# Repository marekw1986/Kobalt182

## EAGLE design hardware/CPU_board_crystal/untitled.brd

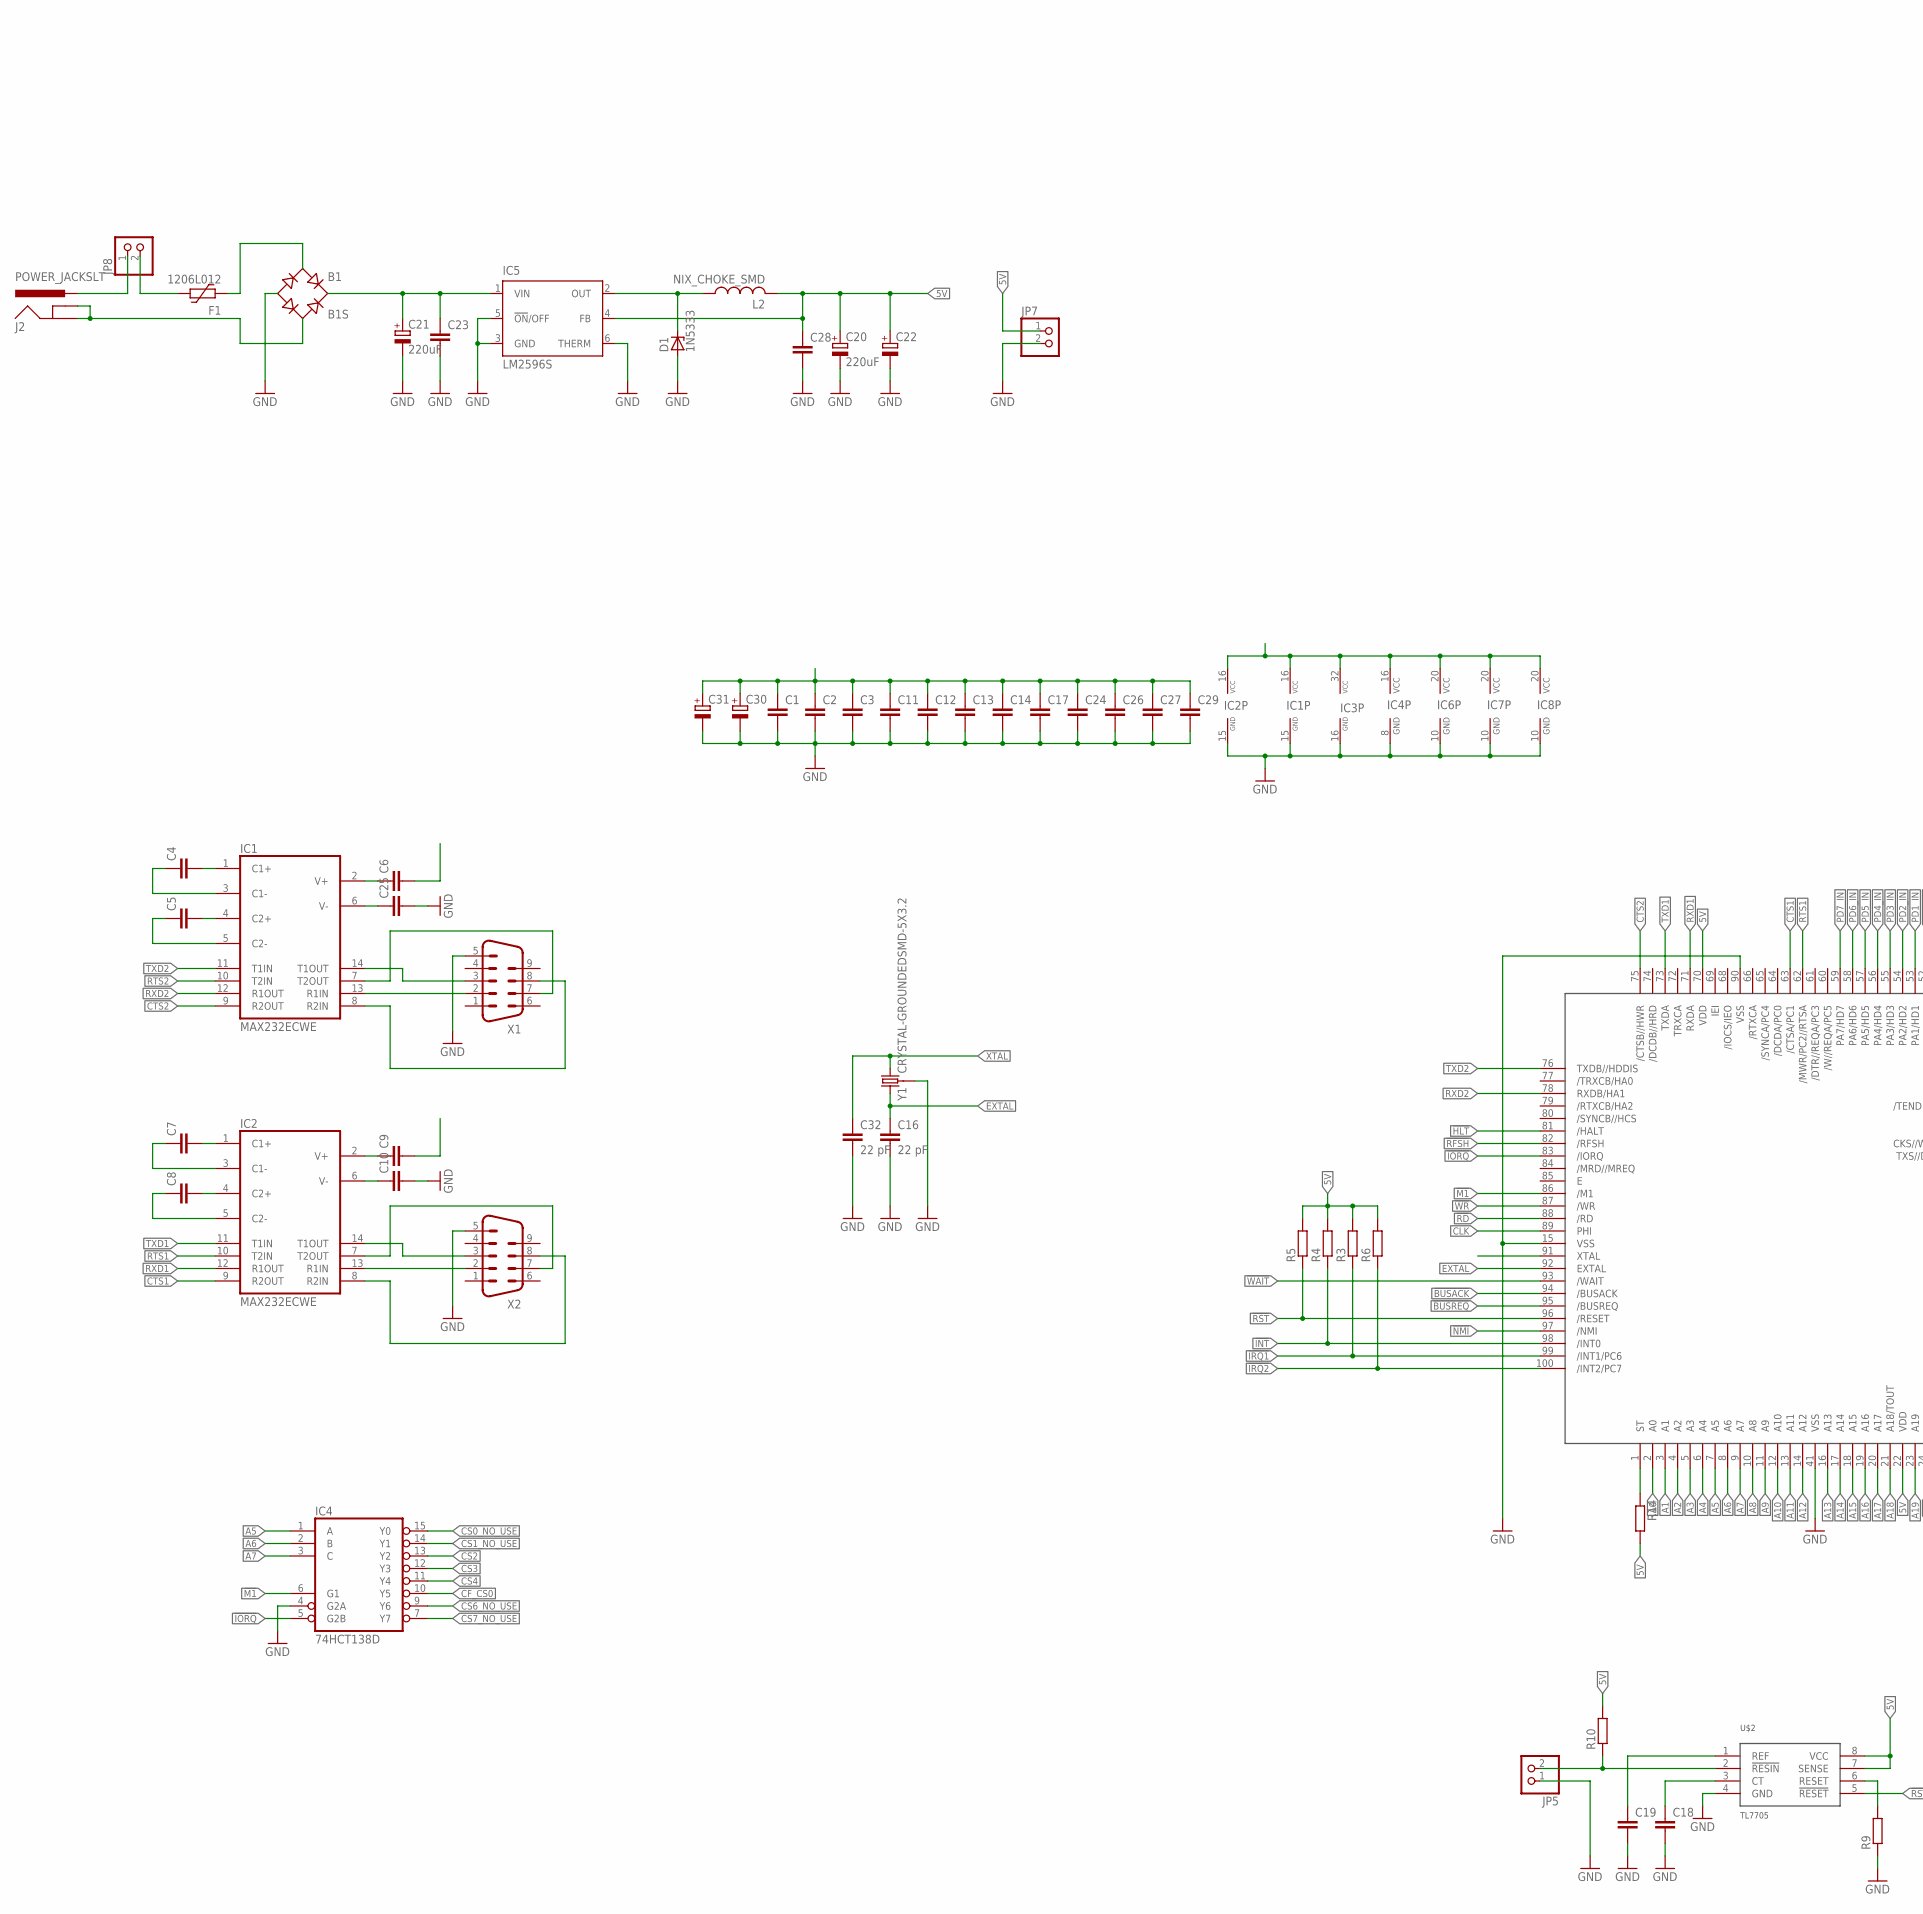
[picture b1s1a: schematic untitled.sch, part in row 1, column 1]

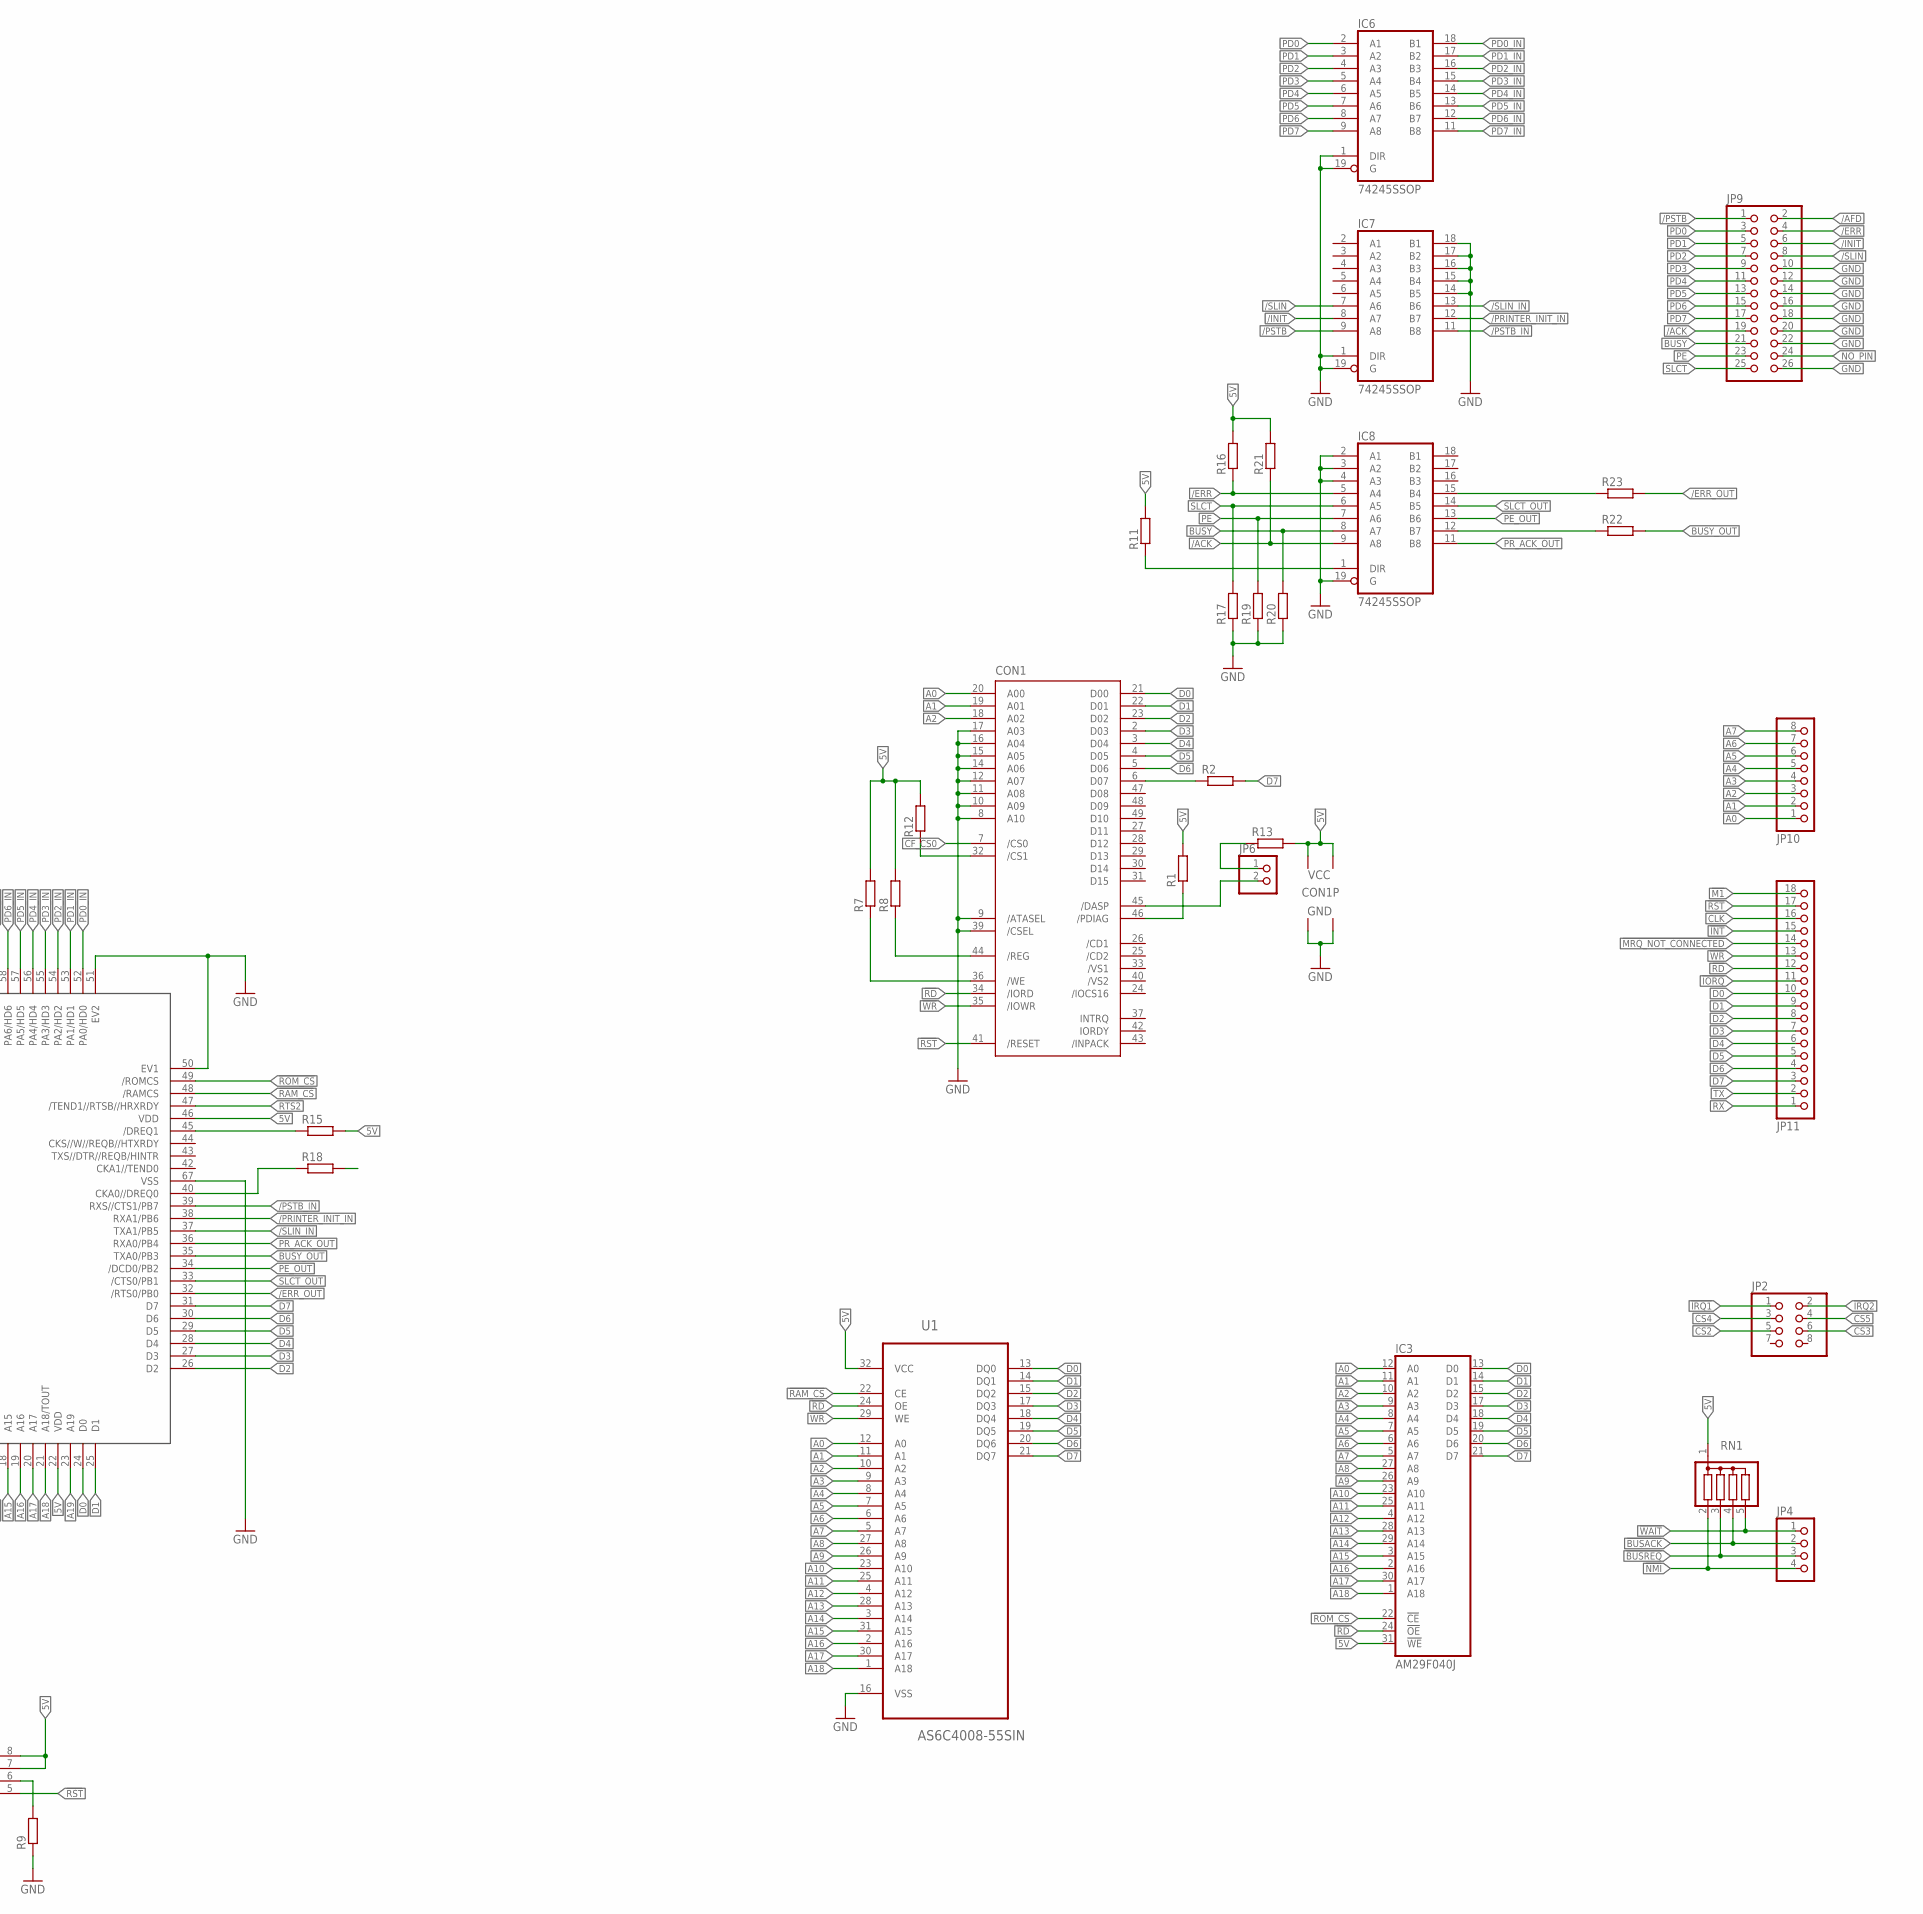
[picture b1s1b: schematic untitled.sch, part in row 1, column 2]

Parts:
B1: B1S; MBS
C1, C2, C4, C5, C6, C7, C8, C9, C10, C11, C12, C14, C17, C18, C19, C23, C24, C25, C28, C29: C-EUC0603; C0603
C3, C13, C26, C27: C-EUC0402; C0402
C16, C32: 22 pF; C0603
C20, C21: 220uF; 153CLV-0810
C22: CPOL-EUSMCC; SMC_C
C30, C31: CPOL-EUSMCB; SMC_B
CON1: CF-CARD-IDE_MODE; MI20-50PD-SF
D1: 1N5333; C1702-15
F1: 1206L012; 1206L
IC1, IC2: MAX232ECWE; SO16L
IC3: AM29F040J; PLCC32R
IC4: 74HCT138D; SO16
IC5: LM2596S; TO263-5
IC6, IC7, IC8: 74245SSOP; SSOP20
J2: POWER_JACKSLT; POWER_JACK_SLOT
JP2: PINHD-2X4; 2X04
JP4: PINHD-1X4; 1X04
JP5, JP6, JP7, JP8: PINHD-1X2; 1X02
JP9: PINHD-2X13_2.54-SMD; 2X13SMD
JP10: PINHD-1X8; 1X08
JP11: PINHD-1X18; 1X18
L2: NIX_CHOKE_SMD
R1, R2, R4, R6, R7, R8, R9, R11, R12, R13, R16, R17, R19, R20, R21: R-EU_R0603; R0603
R3, R15, R18, R22, R23: R-EU_R0402; R0402
R5: R-EU_R1206; R1206
R10: R-EU_M1206; M1206
R14: R-EU_0204/5; 0204/5
RN1: G04R; SIL5
U1: AS6C4008-55SIN; SOIC127P1407X299-32N
U$1: Z80182; TQFP100
U$2: TL7705; SOIC8
X1, X2: M09HP
Y1: CRYSTAL-GROUNDEDSMD-5X3.2; CRYSTAL-SMD-5X3.2-4PAD

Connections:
5V: C1.1, C2.1, C3.1, C6.2, C9.2, C11.1, C12.1, C13.1, C14.1, C17.1, C20.+, C22.+, C24.1, C26.1, C27.1, C28.1, C29.1, C30.+, C31.+, CON1.13 (VCC2), CON1.38 (VCC1), IC1.16 (VCC), IC2.16 (VCC), IC3.31 (!WE), IC3.32 (VCC), IC4.16 (VCC), IC5.4 (FB), IC6.20 (VCC), IC7.20 (VCC), IC8.20 (VCC), JP7.1, L2.P$2 (2), R1.2, R3.2, R4.2, R5.2, R6.2, R7.2, R8.2, R10.2, R11.2, R12.2, R13.2, R14.2, R15.2, R16.2, R18.2, R21.2, RN1.1, U1.32 (VCC), U$1.22 (VDD), U$1.46 (VDD), U$1.70 (VDD), U$2.7 (SENSE), U$2.8 (VCC)
!BUSACK: JP4.2, RN1.4, U$1.94 (/BUSACK)
!BUSREQ: JP4.3, RN1.3, U$1.95 (/BUSREQ)
!HLT: U$1.81 (/HALT)
!INT: JP11.15, R4.1, U$1.98 (/INT0)
!IORQ: IC4.5 (G2B), JP11.11, U$1.83 (/IORQ)
!IRQ1: JP2.1, R3.1, U$1.99 (/INT1/PC6)
!IRQ2: JP2.2, R6.1, U$1.100 (/INT2/PC7)
!M1: IC4.6 (G1), JP11.18, U$1.86 (/M1)
!MRQ_NOT_CONNECTED: JP11.14
!NMI: JP4.4, RN1.2, U$1.97 (/NMI)
!RAM_CS: U1.22 (CE), U$1.48 (/RAMCS)
!RD: CON1.34 (/IORD), IC3.24 (!OE), JP11.12, U1.24 (OE), U$1.88 (/RD)
!RFSH: U$1.82 (/RFSH)
!ROM_CS: IC3.22 (!CE), U$1.49 (/ROMCS)
!RST: CON1.41 (/RESET), JP11.17, R5.1, U$1.96 (/RESET), U$2.5 (!RESET)
!WAIT: JP4.1, RN1.5, U$1.93 (/WAIT)
!WR: CON1.35 (/IOWR), JP11.13, U1.29 (WE), U$1.87 (/WR)
/ACK: IC8.9 (A8), JP9.19, R21.1
/AFD: JP9.2
/ERR: IC8.5 (A4), JP9.4, R16.1
/ERR_OUT: R23.2, U$1.32 (/RTS0/PB0)
/INIT: IC7.8 (A7), JP9.6
/PRINTER_INIT_IN: IC7.12 (B7), U$1.38 (RXA1/PB6)
/PSTB: IC7.9 (A8), JP9.1
/PSTB_IN: IC7.11 (B8), U$1.39 (RXS//CTS1/PB7)
/SLIN: IC7.7 (A6), JP9.8
/SLIN_IN: IC7.13 (B6), U$1.37 (TXA1/PB5)
A0: CON1.20 (A00), IC3.12 (A0), JP10.1, U1.12 (A0), U$1.2 (A0)
A1: CON1.19 (A01), IC3.11 (A1), JP10.2, U1.11 (A1), U$1.3 (A1)
A2: CON1.18 (A02), IC3.10 (A2), JP10.3, U1.10 (A2), U$1.4 (A2)
A3: IC3.9 (A3), JP10.4, U1.9 (A3), U$1.5 (A3)
A4: IC3.8 (A4), JP10.5, U1.8 (A4), U$1.6 (A4)
A5: IC3.7 (A5), IC4.1 (A), JP10.6, U1.7 (A5), U$1.7 (A5)
A6: IC3.6 (A6), IC4.2 (B), JP10.7, U1.6 (A6), U$1.8 (A6)
A7: IC3.5 (A7), IC4.3 (C), JP10.8, U1.5 (A7), U$1.9 (A7)
A8: IC3.27 (A8), U1.27 (A8), U$1.10 (A8)
A9: IC3.26 (A9), U1.26 (A9), U$1.11 (A9)
A10: IC3.23 (A10), U1.23 (A10), U$1.12 (A10)
A11: IC3.25 (A11), U1.25 (A11), U$1.13 (A11)
A12: IC3.4 (A12), U1.4 (A12), U$1.14 (A12)
A13: IC3.28 (A13), U1.28 (A13), U$1.16 (A13)
A14: IC3.29 (A14), U1.3 (A14), U$1.17 (A14)
A15: IC3.3 (A15), U1.31 (A15), U$1.18 (A15)
A16: IC3.2 (A16), U1.2 (A16), U$1.19 (A16)
A17: IC3.30 (A17), U1.30 (A17), U$1.20 (A17)
A18: IC3.1 (A18), U1.1 (A18), U$1.21 (A18/TOUT)
A19: U$1.23 (A19)
BUSY: IC8.8 (A7), JP9.21, R20.2
BUSY_OUT: R22.2, U$1.35 (TXA0/PB3)
CF_CS0: CON1.7 (/CS0), IC4.10 (Y5)
CLK: JP11.16, U$1.89 (PHI)
CS0_NO_USE: IC4.15 (Y0)
CS1_NO_USE: IC4.14 (Y1)
CS2: IC4.13 (Y2), JP2.5
CS3: IC4.12 (Y3), JP2.6
CS4: IC4.11 (Y4), JP2.3
CS5: JP2.4
CS6_NO_USE: IC4.9 (Y6)
CS7_NO_USE: IC4.7 (Y7)
CTS1: IC2.9 (R2OUT), U$1.63 (/CTSA/PC1)
CTS2: IC1.9 (R2OUT), U$1.75 (/CTSB//HWR)
D0: CON1.21 (D00), IC3.13 (D0), JP11.10, U1.13 (DQ0), U$1.24 (D0)
D1: CON1.22 (D01), IC3.14 (D1), JP11.9, U1.14 (DQ1), U$1.25 (D1)
D2: CON1.23 (D02), IC3.15 (D2), JP11.8, U1.15 (DQ2), U$1.26 (D2)
D3: CON1.2 (D03), IC3.17 (D3), JP11.7, U1.17 (DQ3), U$1.27 (D3)
D4: CON1.3 (D04), IC3.18 (D4), JP11.6, U1.18 (DQ4), U$1.28 (D4)
D5: CON1.4 (D05), IC3.19 (D5), JP11.5, U1.19 (DQ5), U$1.29 (D5)
D6: CON1.5 (D06), IC3.20 (D6), JP11.4, U1.20 (DQ6), U$1.30 (D6)
D7: IC3.21 (D7), JP11.3, R2.2, U1.21 (DQ7), U$1.31 (D7)
EXTAL: C16.1, U$1.92 (EXTAL), Y1.3 (1)
GND: B1.-, C1.2, C2.2, C3.2, C10.2, C11.2, C12.2, C13.2, C14.2, C16.2, C17.2, C18.2, C19.2, C20.-, C21.-, C22.-, C23.2, C24.2, C25.2, C26.2, C27.2, C28.2, C29.2, C30.-, C31.-, C32.2, CON1.1 (GND1), CON1.8 (A10), CON1.9 (/ATASEL), CON1.10 (A09), CON1.11 (A08), CON1.12 (A07), CON1.14 (A06), CON1.15 (A05), CON1.16 (A04), CON1.17 (A03), CON1.39 (/CSEL), CON1.50 (GND2), D1.A, IC1.15 (GND), IC2.15 (GND), IC3.16 (GND), IC4.4 (G2A), IC4.8 (GND), IC5.3 (GND), IC5.5 (!ON!/OFF), IC5.6 (THERM), IC6.1 (DIR), IC6.10 (GND), IC6.19 (G), IC7.1 (DIR), IC7.10 (GND), IC7.14 (B5), IC7.15 (B4), IC7.16 (B3), IC7.17 (B2), IC7.18 (B1), IC7.19 (G), IC8.2 (A1), IC8.3 (A2), IC8.4 (A3), IC8.10 (GND), IC8.19 (G), JP5.1, JP7.2, JP9.10, JP9.12, JP9.14, JP9.16, JP9.18, JP9.20, JP9.22, JP9.26, R9.1, R17.1, R19.1, R20.1, U1.16 (VSS), U$1.15 (VSS), U$1.41 (VSS), U$1.50 (EV1), U$1.51 (EV2), U$1.67 (VSS), U$1.90 (VSS), U$2.4 (GND), X1.5, X2.5, Y1.2 (3), Y1.4 (3)
unnamed: IC2.7 (T2OUT), X2.7
unnamed: C7.2, IC2.1 (C1+)
unnamed: C8.2, IC2.4 (C2+)
unnamed: C8.1, IC2.5 (C2-)
unnamed: C7.1, IC2.3 (C1-)
unnamed: C9.1, IC2.2 (V+)
unnamed: IC1.7 (T2OUT), X1.7
unnamed: IC1.13 (R1IN), X1.2
unnamed: C4.2, IC1.1 (C1+)
unnamed: C5.2, IC1.4 (C2+)
unnamed: C5.1, IC1.5 (C2-)
unnamed: C4.1, IC1.3 (C1-)
unnamed: C6.1, IC1.2 (V+)
unnamed: C25.1, IC1.6 (V-)
unnamed: IC2.13 (R1IN), X2.2
unnamed: IC2.14 (T1OUT), X2.3
unnamed: IC2.8 (R2IN), X2.8
unnamed: IC1.14 (T1OUT), X1.3
unnamed: C10.1, IC2.6 (V-)
unnamed: J2.PWR, JP8.1
unnamed: B1.AC1, F1.2
unnamed: B1.+, C21.+, C23.1, IC5.1 (VIN)
unnamed: D1.C, IC5.2 (OUT), L2.P$1 (1)
unnamed: B1.AC2, J2.GND@1 (GNDBREAK), J2.GND@2 (GND)
unnamed: R15.1, U$1.45 (/DREQ1)
unnamed: IC8.1 (DIR), R11.1
unnamed: CON1.44 (/REG), R8.1
unnamed: IC1.8 (R2IN), X1.8
unnamed: CON1.36 (/WE), R7.1
unnamed: CON1.46 (/PDIAG), R1.1
unnamed: CON1.32 (/CS1), R12.1
unnamed: JP6.1, R13.1
unnamed: CON1.45 (/DASP), JP6.2
unnamed: CON1.6 (D07), R2.1
unnamed: R9.2, U$2.6 (RESET)
unnamed: C18.1, U$2.3 (CT)
unnamed: C19.1, U$2.1 (REF)
unnamed: JP5.2, R10.1, U$2.2 (!RESIN)
unnamed: F1.1, JP8.2
unnamed: R18.1, U$1.40 (CKA0//DREQ0)
unnamed: IC8.12 (B7), R22.1
unnamed: IC8.15 (B4), R23.1
NO_PIN: JP9.24
PD0: IC6.2 (A1), JP9.3
PD0_IN: IC6.18 (B1), U$1.52 (PA0/HD0)
PD1: IC6.3 (A2), JP9.5
PD1_IN: IC6.17 (B2), U$1.53 (PA1/HD1)
PD2: IC6.4 (A3), JP9.7
PD2_IN: IC6.16 (B3), U$1.54 (PA2/HD2)
PD3: IC6.5 (A4), JP9.9
PD3_IN: IC6.15 (B4), U$1.55 (PA3/HD3)
PD4: IC6.6 (A5), JP9.11
PD4_IN: IC6.14 (B5), U$1.56 (PA4/HD4)
PD5: IC6.7 (A6), JP9.13
PD5_IN: IC6.13 (B6), U$1.57 (PA5/HD5)
PD6: IC6.8 (A7), JP9.15
PD6_IN: IC6.12 (B7), U$1.58 (PA6/HD6)
PD7: IC6.9 (A8), JP9.17
PD7_IN: IC6.11 (B8), U$1.59 (PA7/HD7)
PE: IC8.7 (A6), JP9.23, R19.2
PE_OUT: IC8.13 (B6), U$1.34 (/DCD0/PB2)
PR_ACK_OUT: IC8.11 (B8), U$1.36 (RXA0/PB4)
RTS1: IC2.10 (T2IN), U$1.62 (/MWR/PC2//RTSA)
RTS2: IC1.10 (T2IN), U$1.47 (/TEND1//RTSB//HRXRDY)
RX: JP11.1
RXD1: IC2.12 (R1OUT), U$1.71 (RXDA)
RXD2: IC1.12 (R1OUT), U$1.78 (RXDB/HA1)
SLCT: IC8.6 (A5), JP9.25, R17.2
SLCT_OUT: IC8.14 (B5), U$1.33 (/CTS0/PB1)
ST: R14.1, U$1.1 (ST)
TX: JP11.2
TXD1: IC2.11 (T1IN), U$1.73 (TXDA)
TXD2: IC1.11 (T1IN), U$1.76 (TXDB//HDDIS)
XTAL: C32.1, U$1.91 (XTAL), Y1.1 (2)

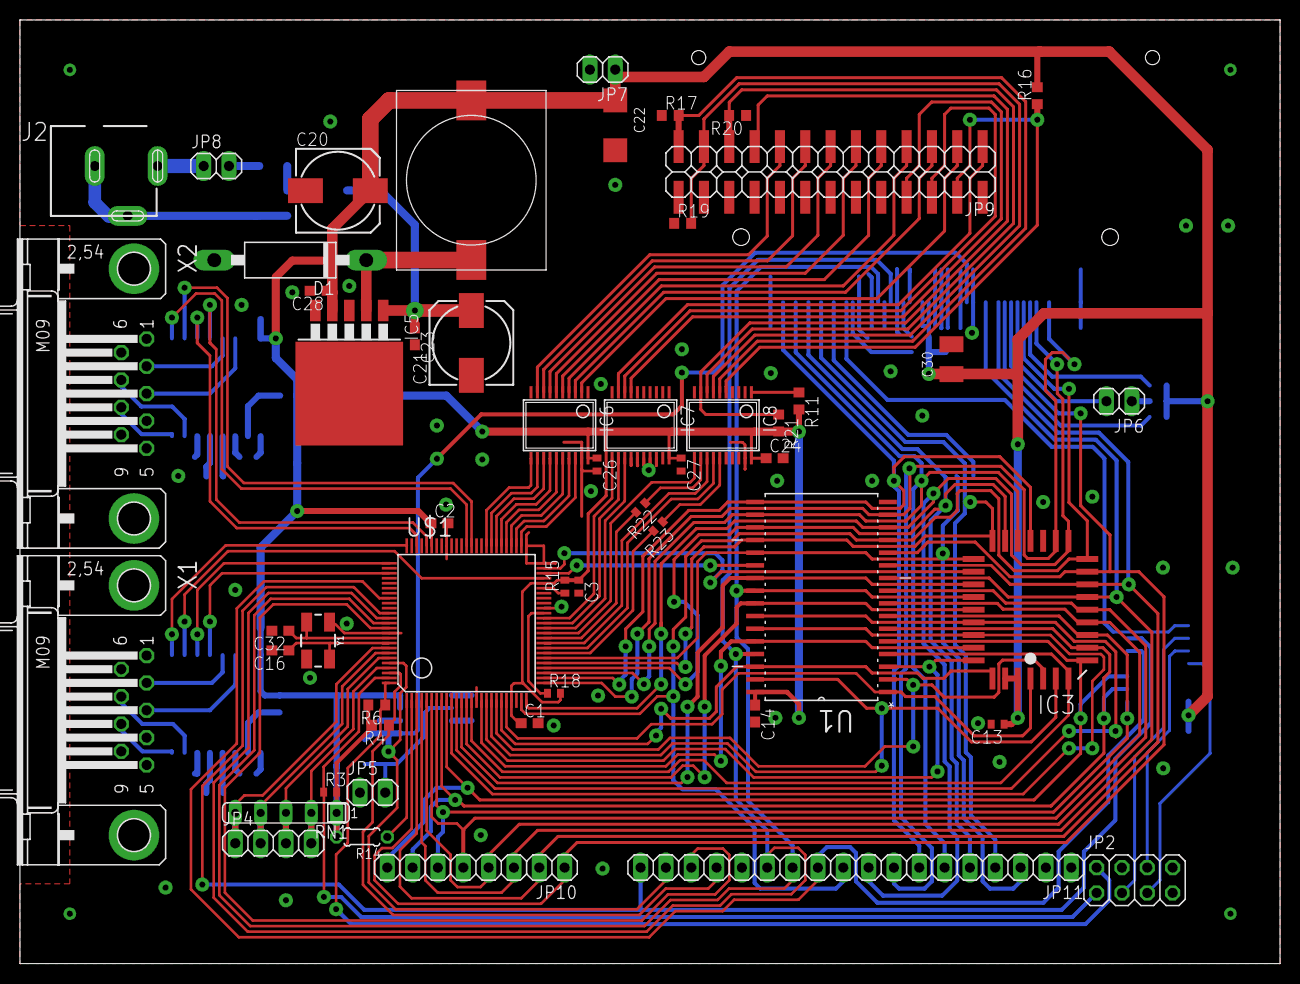
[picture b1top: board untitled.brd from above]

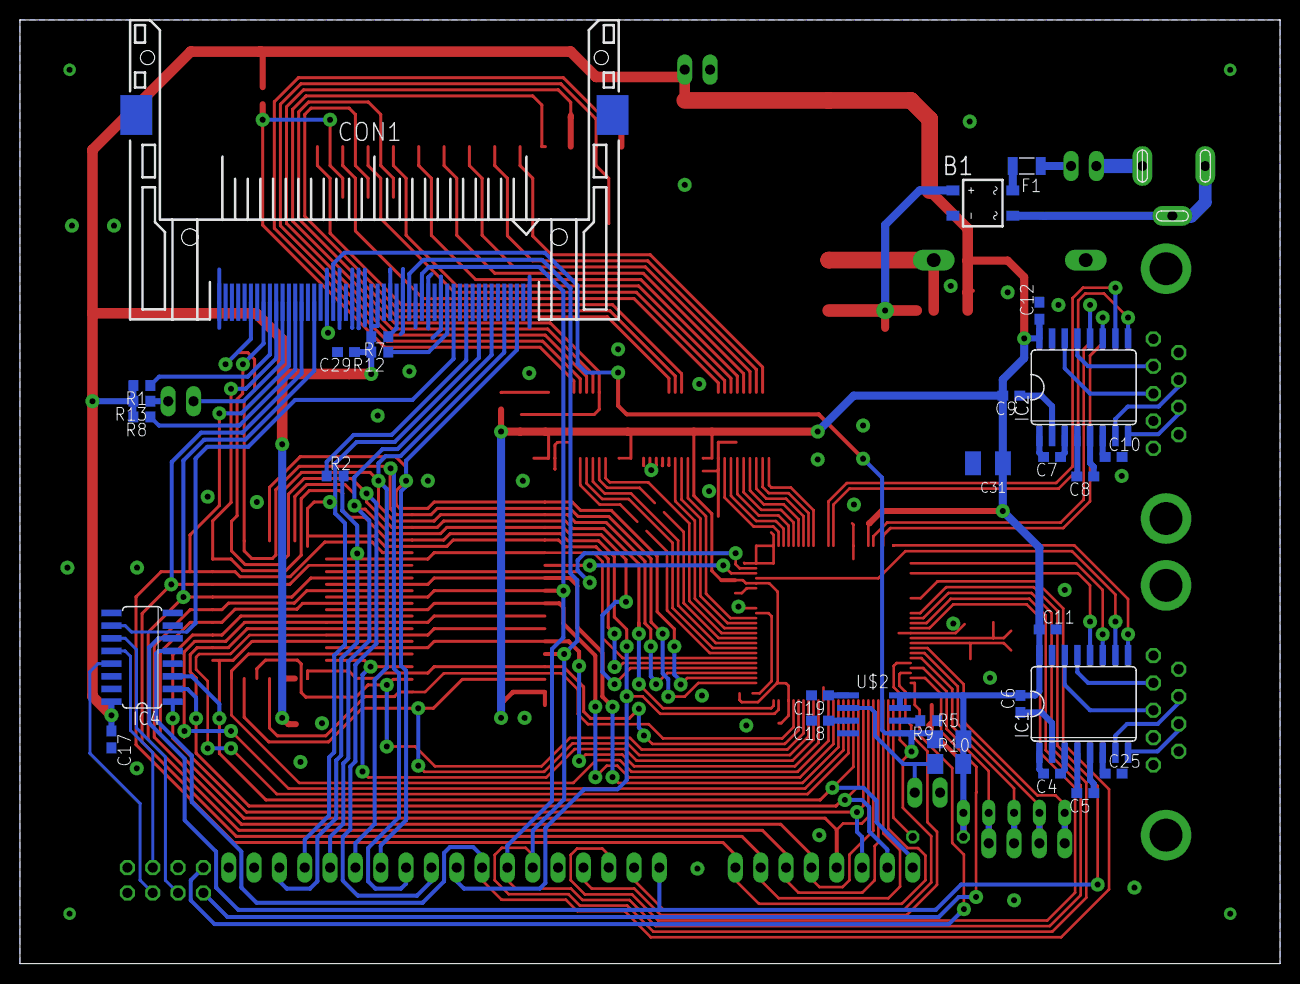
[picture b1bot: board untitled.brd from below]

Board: 2 copper layers, 126.3 x 94.6 mm, 84 parts (31 on the bottom side), 133 nets.

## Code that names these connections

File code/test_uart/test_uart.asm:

        INCL "../common/definitions.asm"

        ORG   00000H
START:
        DI

        ; ----------------------------
        ; MMU / RAM mapping
        ; ----------------------------
        ; --- Program ROM window (0x0000–0x7FFF) ---
        MVI   A, 07H        ; upper block = 0x07 (0x7000–0x7FFF)
        OUT   ROMBR         ; I/O E8h

        ; --- Program RAM window (0x8000–0xFFFF) ---
        MVI   A, 08H        ; lower block = 0x08 (0x8000)
        OUT   RAMLBR        ; I/O E7h
        MVI   A, 0FH        ; upper block = 0x0F (0xF000–0xFFFF)
        OUT   RAMUBR        ; I/O E6h

        ; Configure Wait State Generator
        XRA A
        DB 0EDH, 039H, 032H     ; OUT0 32H
        MVI   A, 88H        
        OUT   WSG           ; I/O addr 0xD8

        ; Small delay to let bus decode settle (optional)
        NOP
        NOP
        
        MVI	  A, 04H		; Normal (level based detection for INT1 and INT2, MREQ, RTSA/PC2, IOCS, no low noise, no wait delay on HALT,
        OUT	  IEPMR
        
        ; ----------------------------
        ; Init PIO Port A
        ; ----------------------------
		; Set Port B to GPIO (parallel)
        MVI   A, 60H      ; SCR bit 7 = 0, bit 6 = 1, bit 5 = 1, other bits = 0
        OUT   SCR         ; Use definitions.asm to define SCR
        ; Configure all lines as outputs
        XRA A
        OUT   PADIR            ; use label from definitions.asm
        ; Ensure all PA lines low
        XRA A
        OUT   PADATA            ; use label from definitions.asm
        
        MVI   A, 1FH                ; PB0..Pb4 inputs, PB5..PB7 outputs
        OUT   PBDIR
        XRA A
        OUT   PBDATA

        ; Setup stack to top of mapped RAM
        LXI   H, 0FFDFH       ; Stack top
        SPHL
        
        NOP
        NOP
        NOP

; --- Reset channel A ---
        MVI   A, 09h           ; WR9 (Reset and interrupt ESCC_A_CTRL)
        OUT   ESCC_A_CTRL
        MVI   A, 0C0h          ; Reset Channel A + Tx underrun
        OUT   ESCC_A_CTRL

; --- Async mode (8N1) ---
        MVI   A, 04h           ; Select WR4
        OUT   ESCC_A_CTRL
        MVI   A, 44h          ; 16× clock, 1 stop bit, 8 bits, async
        OUT   ESCC_A_CTRL

; --- Disable Rx (clear receiver parameters) ---
        MVI   A, 03h           ; Select WR3
        OUT   ESCC_A_CTRL
        XRA A           ; Rx disabled
        ;MVI	  A, 01h		   ; Rx enabled
        OUT   ESCC_A_CTRL

; --- Enable Tx (and RTS) ---
        MVI   A, 05h           ; Select WR5
        OUT   ESCC_A_CTRL
        MVI   A, 0EAh          ; Tx enable, RTS, DTR 8-bit — 1110 1010b
        OUT   ESCC_A_CTRL

; --- Baud rate generator (BRG) setup ---
        ; Divisor ≈ 651 for 9600 baud @ 12.5 MHz clock
        MVI   A, 0Ch           ; Select WR12 (BRG low byte)
        OUT   ESCC_A_CTRL
        MVI   A, 08Bh          ; Low byte = 0x8B (139)
        OUT   ESCC_A_CTRL

        MVI   A, 0Dh           ; Select WR13 (BRG high byte)
        OUT   ESCC_A_CTRL
        MVI   A, 02h           ; High byte = 0x02 (2)
        OUT   ESCC_A_CTRL

        MVI   A, 0Eh           ; Select WR14 (BRG ESCC_A_CTRL)
        OUT   ESCC_A_CTRL
        MVI   A, 03h           ; Enable BRG and set clock source
        OUT   ESCC_A_CTRL

LOOP:
        MVI   A, 055h          ; ESCC_A_DATA to send
        CALL OUT_CHAR             
        
        MVI   A, 0FFH
        OUT   PADATA
        
		MVI	  A, 255
		CALL  DELAY
        
        XRA A
        OUT   PADATA
        
        MVI   A, 255
        CALL DELAY
		
        JMP   LOOP

		INCL "../common/utils.asm"

        END

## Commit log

2025-05-30 PCB updated
2025-06-06 PCB project updated (work in progress)
2025-06-06 PBC project updated (work in progress)
2025-06-06 PCB update (work in progress)
2025-06-06 PCB update
2025-06-07 Minor update in PCB design
2025-06-08 Minor fix
2025-06-08 PCB updated - data lines routed (work in progress)
2025-06-09 PCB project update (work in progress)
2025-06-09 CF card socket added (work in progress)
2025-06-11 PCB update - I/O address decoder added (work in progress)
2025-06-11 Minor PCB update (work in progress)
2025-06-11 CPU board update (work in progress)
2025-06-13 Minor changes in PCB design
2025-06-13 PCB edit (work in progress)
2025-06-15 PCB design updated. NMI, WAIT, BUSREQ and BUSACK signals routed to additional connector
2025-06-16 Resistor network added
2025-06-17 Pullup resistors added
2025-06-17 I/O address decoder adjusted to internal registers of Z80182
2025-06-19 Reset supervisor added, GND tracing changed
2025-06-19 Reset circuit updated
2025-06-19 Connector instead LED on board
2025-06-22 Power circuit updated
2025-06-29 Printer port (work in progress)
2025-06-30 Buffer added on printer port data lines
2025-07-01 Minor change on PCB
2025-07-01 Another buffer added to printer port
2025-07-03 Power trace updated
2025-07-03 Additional printer traces routed
2025-07-04 VCC rerouted
2025-07-04 Printer port wired
2025-07-04 Printer error line routed
2025-07-04 Capacitors added
2025-07-04 Minor changes
2025-07-04 Mounting holes added, board size adjusted
2025-07-05 Dangling signals fixed
2025-07-05 ST signal connected (work in progress)
2025-07-06 Pull-up on ST and DREQ lines added
2025-07-07 Debug LED added
2025-07-08 GND and VCC pins removed from bottom bus connector to prevent GND loop
2025-08-01 File definitions.asm added - addresses of Z80182 registers
2025-08-01 Bug in hardware design fixed - CF card address moved, upper I/O addreses not used due to conflict with internal registers
2025-08-01 Crystal resonator replaced with crystal generator
2025-08-26 blink and test uart added
2025-08-28 Blink update
2025-08-31 Minor update
2025-09-01 Recent changes
2025-09-01 Blink updated
2025-09-03 Test code updated
2025-09-04 Changes in test_uart
2025-09-04 Style change
2025-09-04 CP/m CF bootloader added
2025-09-05 Config changes in test_uart t oenable RTSA pin
2025-09-11 MVI A, 00H replaced with XOR A to preserve memory and CPU cycles
2025-09-11 CPI 00H replaced with OR A
2025-09-11 Revert "CPI 00H replaced with OR A"
    This reverts commit 459384876c93d7001f2c2da0981e63e3da6e4703.
2025-09-11 Revert "MVI A, 00H replaced with XOR A to preserve memory and CPU cycles"
    This reverts commit 5c4637fd88a033c001f39b4de0042432ee14601f.
2025-09-11 MVI A, 00H replaced with XRA A
2025-09-13 Fixed in blink_stack, Z180 version prepared
2025-09-14 Configuration of Port B added
2025-09-15 test_uart moved to asl from a85 and ported to z180
2025-09-15 blink_count added
2025-09-15 test_uart optimized with Z180 OUT0 instruction
2025-09-15 Z180 code optimized with OUT0 instruction
2025-09-15 Stack moved to upper RAM
2025-09-16 UART works
2025-09-16 Address of CF card changed
2025-09-16 Bootloader updated
2025-09-16 CPI 00H replaced with ORA A
2025-09-16 CP/M added
2025-09-16 Classic 8080 CCP restored
2025-09-16 Optimizations
2025-09-16 Unused 8080 code removed
2025-09-17 PCB updated - resistors protecting default output lines at reset
2025-09-17 DREQ0 disconnected from common pull-up with DREQ1 because default function of this pin is CKA0
2025-09-21 Deffered writes. Work in progress. Needs to be tested.
2025-09-21 Code cleaned after introduction of deferred writes
2025-09-21 Minor bug fixed
2025-09-21 Deffered writes bug fixed
2025-09-21 Minor optimization
2025-09-22 Duplicate instructions removed
2025-09-22 Flushing deferred writes in case of CALC_CFLBA_FROM_PART_ADR fail
2025-09-22 Temporary workaround for deffered write issue
2025-09-23 Unused string removed. CF related strings moved to cf.asm
2025-09-23 TMP LBA added
2025-11-09 Bootloader initialization updated to achieve 115200 bps at 33MHz system clock
2025-11-10 NOP added after UART initialization
2025-11-10 PCB fix
2025-11-10 Slight optimization of PCB
2025-11-13 Curout added to avoiding accidental shorting of DB9 socket shield to board ground
2025-11-13 Version of board with regular crystal instead of oscilator added

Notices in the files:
parts and their libraries:
SparkFun-Connectors: Licensing: Creative Commons ShareAlike 4.0 International - https://creativecommons.org/licenses/by-sa/4.0
